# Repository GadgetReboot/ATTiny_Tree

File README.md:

# ATTiny_Tree
ATTiny 85 based Neopixel WS2812B Christmas Tree

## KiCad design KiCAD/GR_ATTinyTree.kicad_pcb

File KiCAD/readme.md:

KiCAD Design files
V1.1 has a rotated battery to clear the obstacles blocking the battery on v1.0

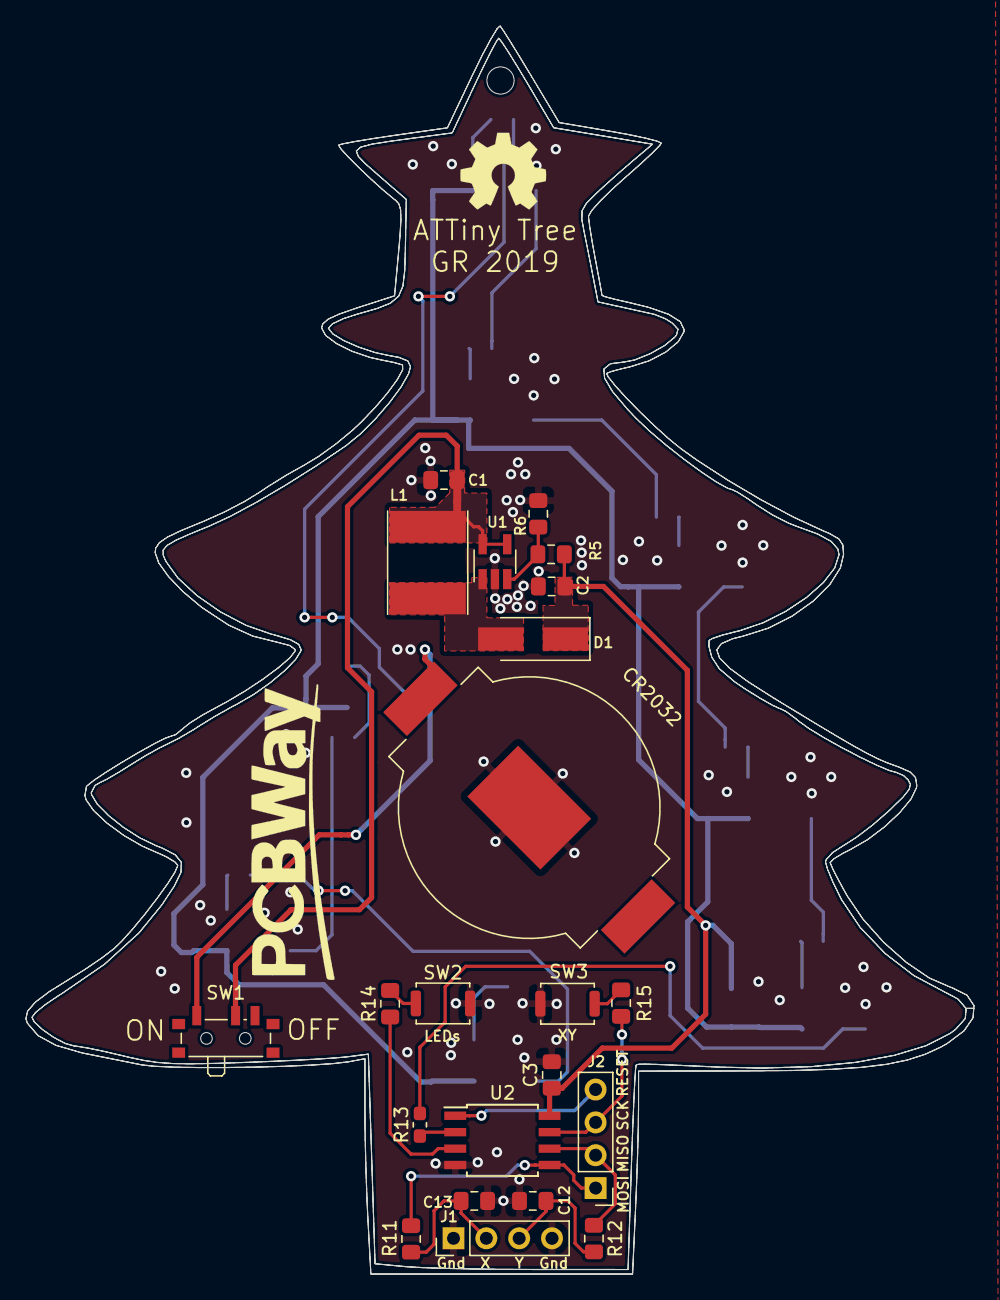
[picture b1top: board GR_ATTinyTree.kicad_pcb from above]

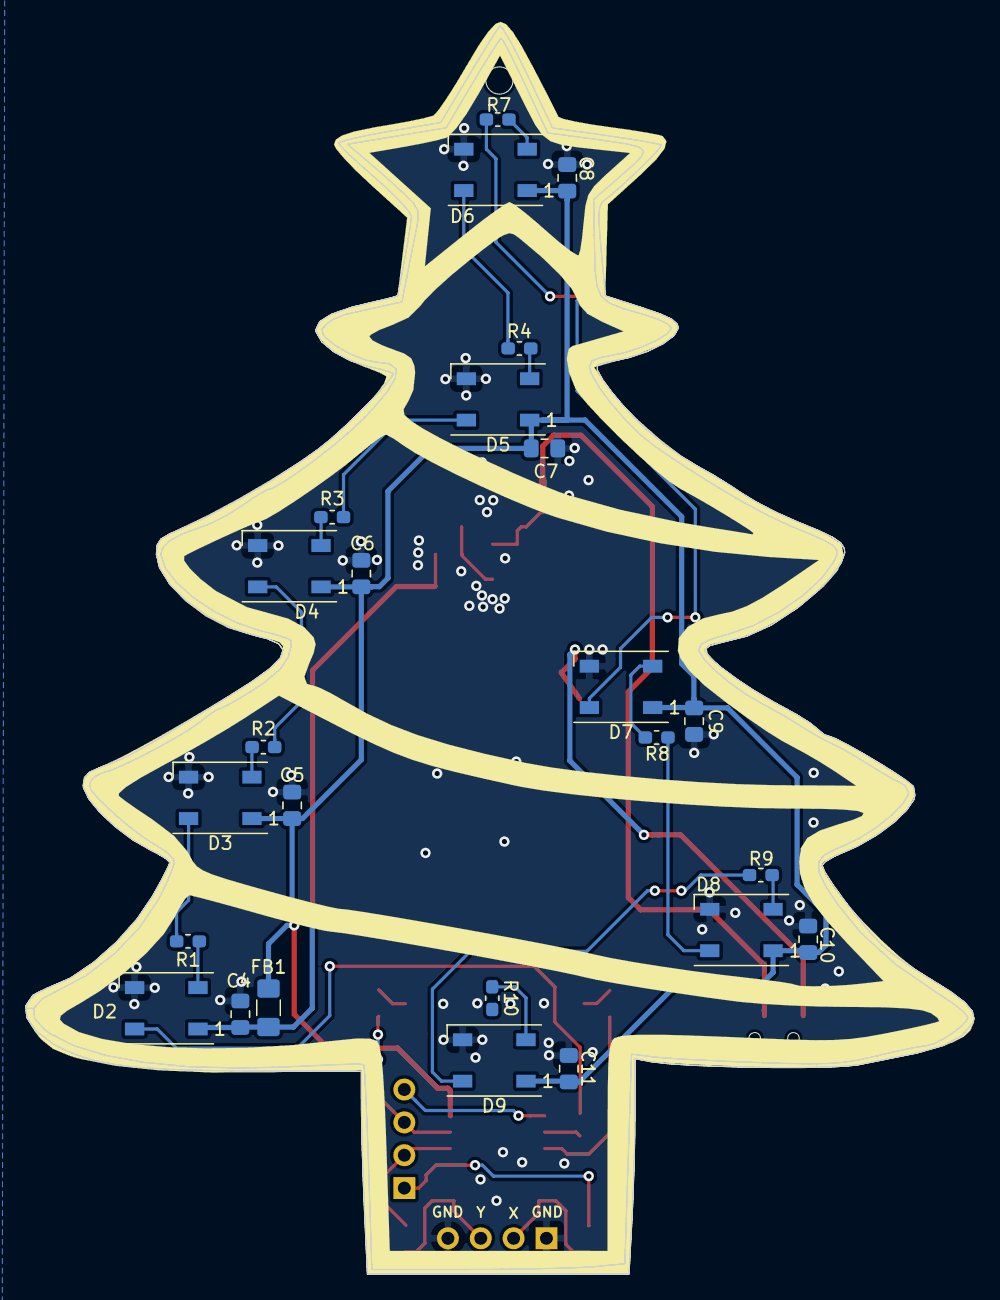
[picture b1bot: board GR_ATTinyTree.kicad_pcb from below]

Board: 2 copper layers, 73.3 x 96.6 mm, 47 parts (25 on the bottom side), 33 nets.

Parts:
Batt1: CR2032; BatteryHolder_MPD_BC2003_1x2032
C1, C2: 4.7uF; C_0805_2012Metric_Pad1.15x1.40mm_HandSolder
C3, C4, C5, C6, C7, C8, C9, C10, C11, C12, C13: 100nF; C_0805_2012Metric_Pad1.15x1.40mm_HandSolder
D1: SK35; D_SMA_Handsoldering
D2, D3, D4, D5, D6, D7, D8, D9: WS2812B; LED_WS2812B_PLCC4_5.0x5.0mm_P3.2mm
FB1: Ferrite_Bead_Small; L_1206_3216Metric_Pad1.42x1.75mm_HandSolder
J1, J2: Conn_01x04; PinHeader_1x04_P2.54mm_Vertical
L1: 22uH; L_Taiyo-Yuden_NR-60xx_HandSoldering
R1, R2, R3, R4, R7, R8, R9, R10, R13: 0r; R_0603_1608Metric_Pad1.05x0.95mm_HandSolder
R5: 91K; R_0805_2012Metric_Pad1.15x1.40mm_HandSolder
R6: 30K; R_0805_2012Metric_Pad1.15x1.40mm_HandSolder
R11, R12: 10K; R_0805_2012Metric_Pad1.15x1.40mm_HandSolder
R14, R15: 220r; R_0805_2012Metric_Pad1.15x1.40mm_HandSolder
SW1: SW_SPST; SW_SPDT_PCM12
SW2, SW3: SW_Push; SW_Push_SPST_NO_Alps_SKRK
U1: AP3012; SOT-23-5_HandSoldering
U2: ATtiny85-20SU; SOIJ-8_5.3x5.3mm_P1.27mm

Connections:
+5V: C2.1, C3.1, D1.1, FB1.2, R5.2, U2.8
/Button: R14.1, U2.3
/MISO: J2.2, R12.1, U2.6
/MOSI: J2.1, R11.1, U2.5
/Pixel: D2.4, R13.2
/SCK: J2.3, R15.1, U2.7
/Xout: C13.1, J1.2, R11.2
/Yout: C12.1, J1.3, R12.2
/nRESET: J2.4, U2.1
GNDREF: Batt1.2, C1.2, C2.2, C3.2, C4.2, C5.2, C6.2, C7.2, C8.2, C9.2, C10.2, C11.2, C12.2, C13.2, D2.3, D3.3, D4.3, D5.3, D6.3, D7.3, D8.3, D9.3, J1.1, J1.4, R6.1, SW2.2, SW3.2, U1.2, U2.4
unnamed: Batt1.1, SW1.1
unnamed: C1.1, L1.1, SW1.2, U1.4, U1.5
unnamed: D1.2, L1.2, U1.1
unnamed: D2.2, R1.1
unnamed: D3.2, R2.1
unnamed: D3.4, R1.2
unnamed: D4.2, R3.1
unnamed: D4.4, R2.2
unnamed: D5.2, R4.1
unnamed: D5.4, R3.2
unnamed: D6.2, R7.1
unnamed: D6.4, R4.2
unnamed: D7.2, R8.1
unnamed: D7.4, R7.2
unnamed: D8.2, R9.1
unnamed: D8.4, R8.2
unnamed: D9.2, R10.1
unnamed: D9.4, R9.2
unnamed: R5.1, R6.2, U1.3
unnamed: R13.1, U2.2
unnamed: R14.2, SW2.1
unnamed: R15.2, SW3.1
VCC: C4.1, C5.1, C6.1, C7.1, C8.1, C9.1, C10.1, C11.1, D2.1, D3.1, D4.1, D5.1, D6.1, D7.1, D8.1, D9.1, FB1.1
